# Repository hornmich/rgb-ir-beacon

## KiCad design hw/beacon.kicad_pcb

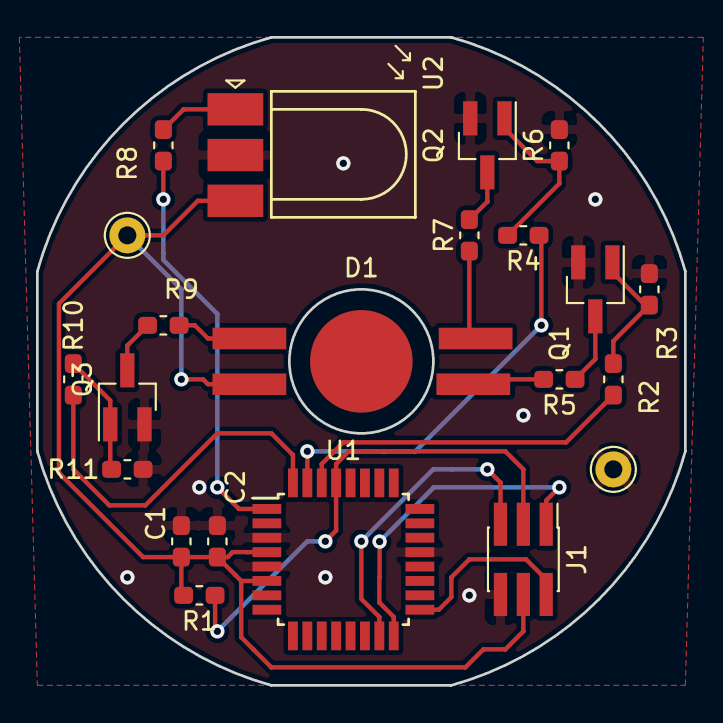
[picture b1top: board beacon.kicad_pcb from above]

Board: 2 copper layers, 36.0 x 36.0 mm, 22 parts (0 on the bottom side), 20 nets.

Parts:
C1, C2: 10n; C_0603_1608Metric_Pad1.05x0.95mm_HandSolder
D1: LED_ARGB; LED_RGB_3W
J1: SPI_Prog_conn; PinHeader_2x03_P1.27mm_Vertical_SMD
MH1: VCC; Pin_D1.0mm_L10.0mm
MH2: GND; Pin_D1.0mm_L10.0mm
Q1, Q2, Q3: Q_NMOS_GSD; SOT-23_Handsoldering
R1, R3, R6, R11: 10k; R_0603_1608Metric_Pad1.05x0.95mm_HandSolder
R2, R4, R8, R10: 100R; R_0603_1608Metric_Pad1.05x0.95mm_HandSolder
R5, R7, R9: 220R; R_0603_1608Metric_Pad1.05x0.95mm_HandSolder
U1: ATmega328-AU; TQFP-32_7x7mm_P0.8mm
U2: TSOP382xx; Vishay_MINIMOLD-3Pin-horizontal-smd

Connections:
/IR_MCU_IN: R8.2, U1.1
/LED_B_MCU_OUT: R10.1, U1.32
/LED_G_MCU_OUT: R4.1, U1.31
/LED_R_MCU_OUT: R2.1, U1.30
/MISO: J1.1, U1.16
/MOSI: J1.5, U1.15
/RST: J1.3, R1.1, U1.29
/SCK: J1.2, U1.17
GND: C1.2, C2.2, J1.6, MH2.1, Q1.2, Q2.2, Q3.2, R3.2, R6.2, R11.2, U1.3, U1.5, U1.21, U2.2
unnamed: D1.2, R5.2
unnamed: D1.3, R7.1
unnamed: D1.4, R9.1
unnamed: Q1.1, R2.2, R3.1
unnamed: Q1.3, R5.1
unnamed: Q2.1, R4.2, R6.1
unnamed: Q2.3, R7.2
unnamed: Q3.1, R10.2, R11.1
unnamed: Q3.3, R9.2
unnamed: R8.1, U2.1
VCC: C1.1, C2.1, D1.1, J1.4, MH1.1, R1.2, U1.4, U1.6, U2.3

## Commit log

2018-09-20 Initial HW design
2018-10-02 Update PCB layout
    Set coordinates origin,
    Fill in document information
    Add alignment target
    Add dimmensions
2018-11-21 Fixed hardware design errors
    Missing connection between IR sensor and MCU
    Wrong footprint for transistors
2018-11-21 Implement IR code reader for Arduino Uno board
    IR sensor to be connected to Pin 13
    Codes on the Serial port.
2018-11-21 Added table of IR codes for the supplied remote controller
2018-11-21 Implement first controller firmware
    Is able to turn on different RGB colors by the remote controller.
2018-11-30 Implement full featured firmware for the beacon
